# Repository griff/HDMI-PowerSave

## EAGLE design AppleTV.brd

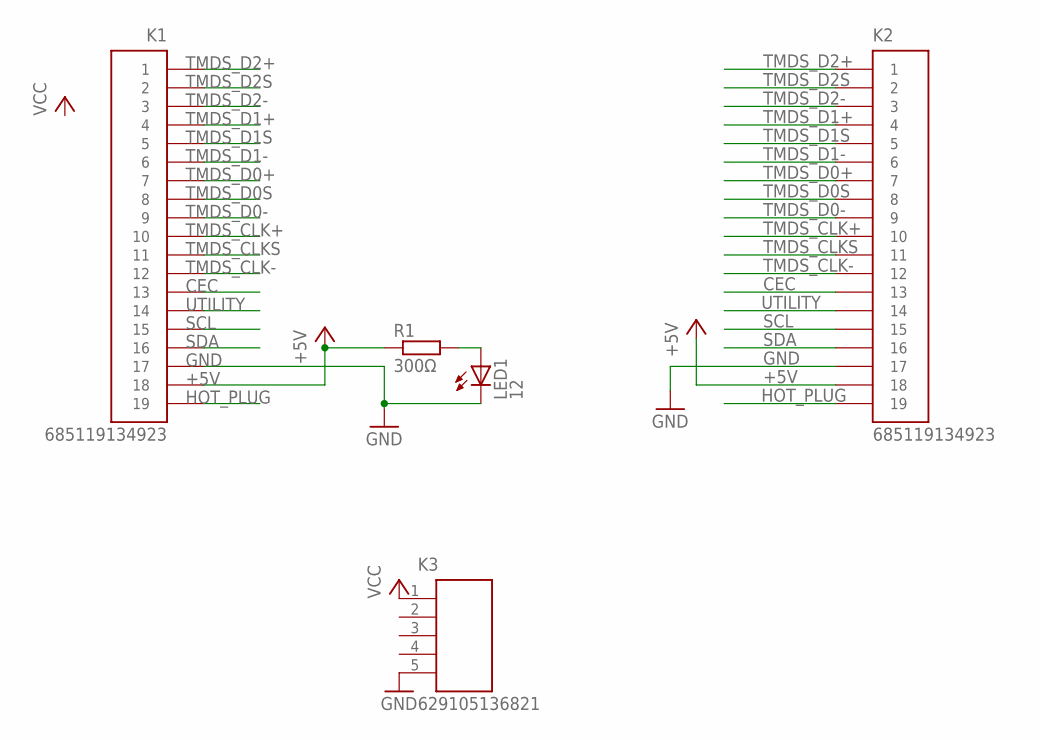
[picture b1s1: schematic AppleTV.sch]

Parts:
K1, K2: 685119134923
K3: 629105136821
LED1: 12; CHIPLED_1206
R1: 300Ω; R0805

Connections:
+5V: K2.18, R1.1
CEC: K1.13, K2.13
GND: K1.17, K2.17, K3.5, LED1.C
HOT_PLUG: K1.19, K2.19
unnamed: LED1.A, R1.2
SCL: K1.15, K2.15
SDA: K1.16, K2.16
TMDS_CLK+: K1.10, K2.10
TMDS_CLK-: K1.12, K2.12
TMDS_CLKS: K1.11, K2.11
TMDS_D0+: K1.7, K2.7
TMDS_D0-: K1.9, K2.9
TMDS_D0S: K1.8, K2.8
TMDS_D1+: K1.4, K2.4
TMDS_D1-: K1.6, K2.6
TMDS_D1S: K1.5, K2.5
TMDS_D2+: K1.1, K2.1
TMDS_D2-: K1.3, K2.3
TMDS_D2S: K1.2, K2.2
UTILITY: K1.14, K2.14
VCC: K3.1

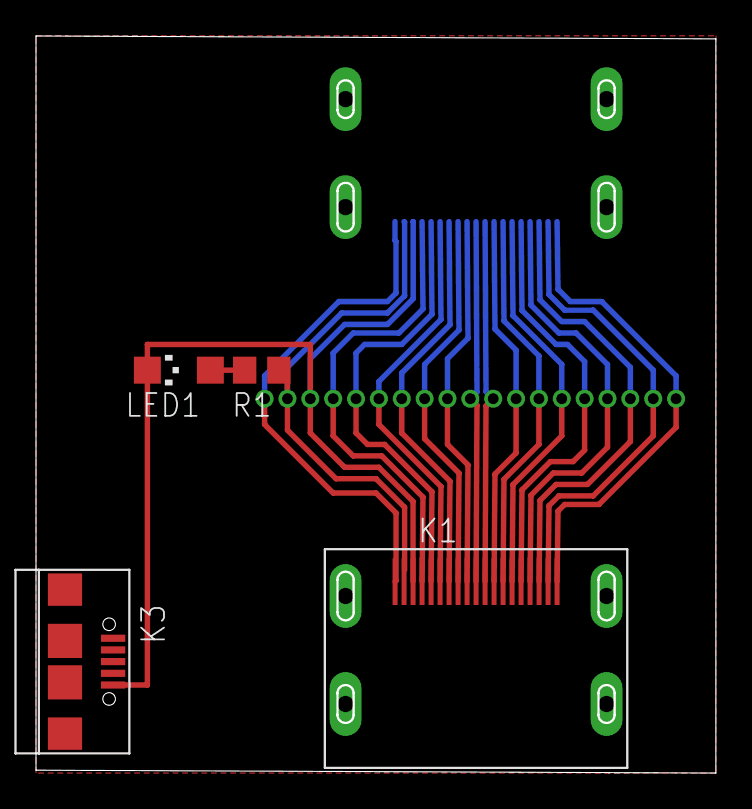
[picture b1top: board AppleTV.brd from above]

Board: 2 copper layers, 37.6 x 40.8 mm, 5 parts (1 on the bottom side), 20 nets.

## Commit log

2016-08-24 Initial import

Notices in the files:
parts and their libraries:
Input-Output_Connectors_rev15d: Copyright: Würth Elektronik
